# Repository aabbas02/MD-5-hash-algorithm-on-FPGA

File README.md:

# Verilog code for MD-5 hash algorithm 
* Verilog implementaiton and testbench of the MD5 algorithm. The MD5 algorithm is implemented as a Moore state machine with 9 states.
* The top module `FGHI.v` takes as input a 128 byte hexadecimal representation of a string.
* The inputs are labelled `M_0[31:0]` through `M_15[31:0]`.
* The 16 byte hash value is output in clocked register `output[127:0]`.
* The testbench code for behavioural simulation is in the file labelled `tb_bench.v`

# Dual layered PCB Design for DB-15 connector
* The schematic of the dual layered PCB for the DB-15 VGA connector was designed using Eagle.
* 40 boards of the design were fabricated.
* The schematic is contained in the folder `DB-15`.

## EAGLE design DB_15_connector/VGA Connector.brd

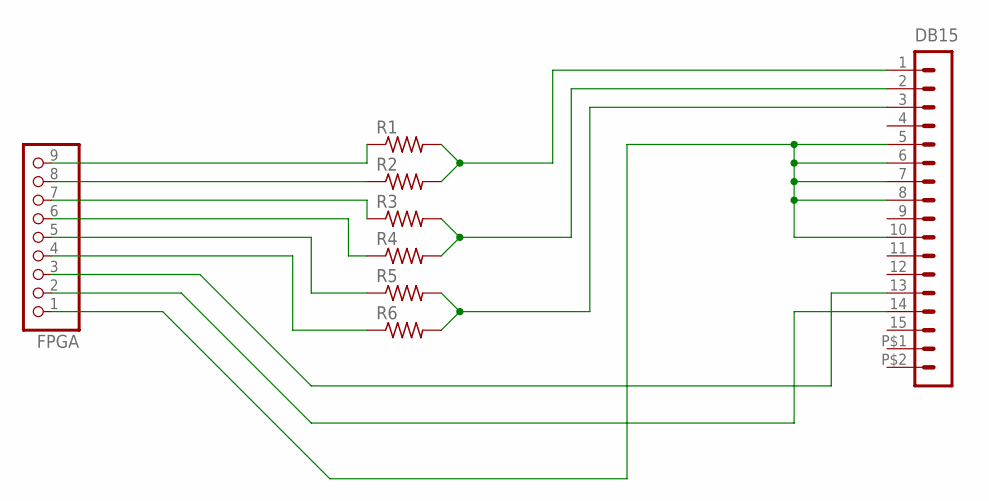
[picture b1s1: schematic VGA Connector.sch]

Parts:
DB15: CON-DSUB-15-VGA; 181-015-212-171
FPGA: PINHD-1X9/90; 1X09/90
R1, R2, R3, R4, R5, R6: R-US_0207/10; 0207/10

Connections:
GND: DB15.5, DB15.6, DB15.7, DB15.8, DB15.10, FPGA.1
unnamed: FPGA.9, R1.1
unnamed: FPGA.8, R2.1
unnamed: FPGA.7, R3.1
unnamed: FPGA.6, R4.1
unnamed: FPGA.5, R5.1
unnamed: FPGA.4, R6.1
unnamed: DB15.13, FPGA.3
unnamed: DB15.14, FPGA.2
unnamed: DB15.1, R1.2, R2.2
unnamed: DB15.2, R3.2, R4.2
unnamed: DB15.3, R5.2, R6.2

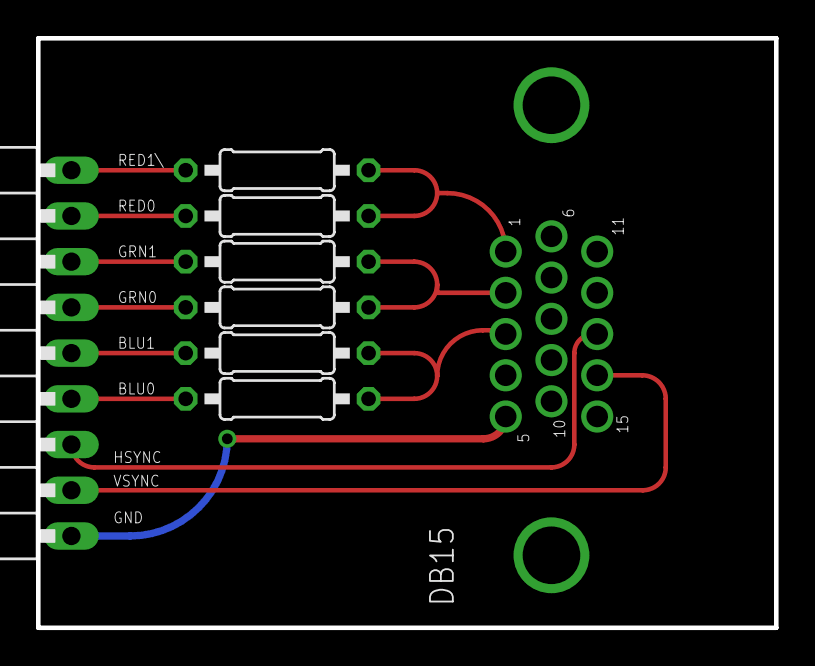
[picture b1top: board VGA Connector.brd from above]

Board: 2 copper layers, 41.0 x 32.8 mm, 8 parts (0 on the bottom side), 12 nets.

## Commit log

2022-01-16 Verilog implementation and testbench for MD5 algorithm
2022-01-16 Verilog implementation of MD5
2022-01-16 PCB schematic for DB-15 connector
2022-01-16 PCB schematic for DB 15 connector
2022-01-17 Rename readme.txt to readme.md

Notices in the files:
parts and their libraries:
m-pad-2.1: License : GNU General Public License version 2 (see bottom)
